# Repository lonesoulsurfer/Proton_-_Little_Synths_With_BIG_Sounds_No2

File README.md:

# Proton - Little Synths With BIG Sounds #2

This is the 2nd in a series of little synths that I'll be publishing over the next couple builds. Like my Elements synth, I've kept everything as simple as possible on this build so anyone with a soldering iron and basic soldering skills can make it. I've done away with a case and fancy power supplies to keep the build simple.

Props to Synther Jack (https://syntherjack.net/totoro-1-ic-simple-synth/) who designed this amazing little synth. All I've done is redesigned the PCB and created a front panel. I've also done a couple of mods and have included these on this build. Please check out Synther Jacks write up if you want a thorough run through on how the synth works.

The synth runs off 1 IC which is an incredible feat when you consider the amazing sounds this beast can produce. The other amazing thing about this synth is it only needs 2 X AA batteries to power it!

It's a blast to play with and can be connected to a sequencer which really shows off the sounds this little synth is capable of producing. If you don't have a sequencer then don't worry - it's still tonnes of fun to play.

Instructables step by step guide: https://www.instructables.com/Proton-Little-Synths-With-BIG-Sounds-2/

YouTube vid: https://www.youtube.com/watch?v=9Ci_B_42n48

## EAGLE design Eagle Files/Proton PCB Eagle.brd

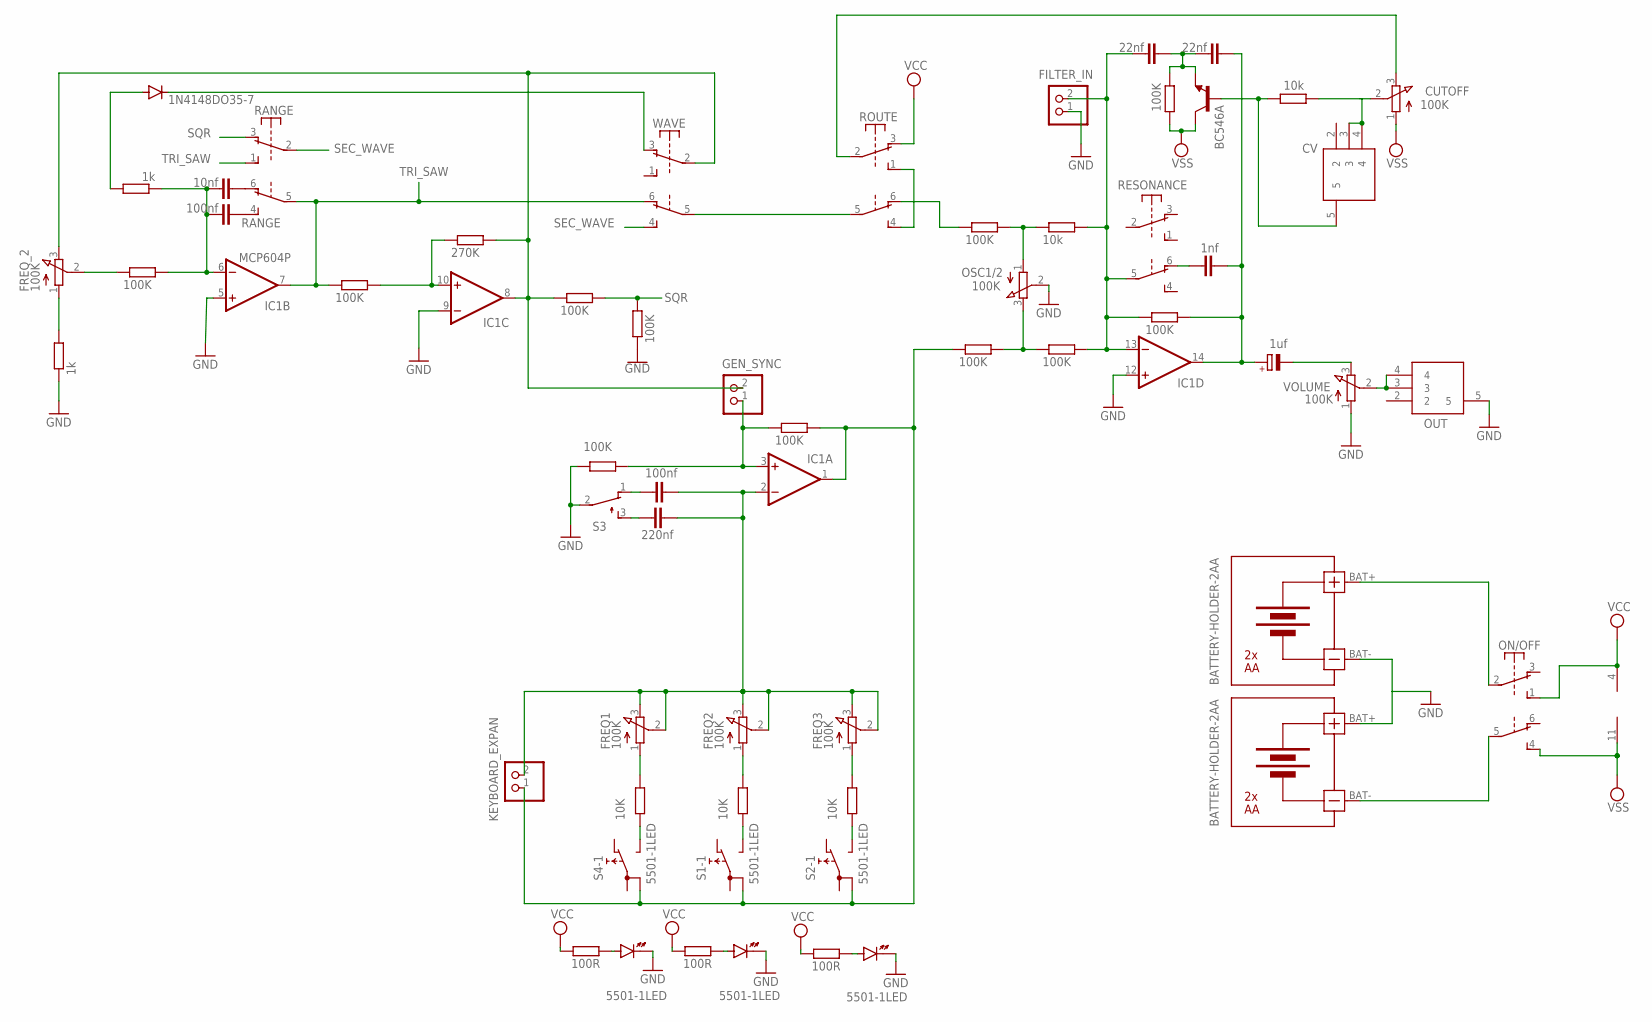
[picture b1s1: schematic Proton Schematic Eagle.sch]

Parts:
1K, 1K1: 1k; 0207/10
100K, 100K1, 100K3, 100K4, 100K5, 100K7, 100K8, 100K9, 100K11, 100K12, 100K13: 100K; 0207/10
100K2: 270K; 0207/10
100K6, 100K10: 10k; 0207/10
100K14, 100K15, 100K16: 10K; 0207/10
100K18, 100K19, 100K20: 100R; 0207/10
C1, C7: 100nf; C050-024X044
C2: 10nf; C050-024X044
C3, C4: 22nf; C050-024X044
C5: 1nf; C050-024X044
C6: 220nf; C050-024X044
C8: 1uf; E2,5-5
CUTOFF: 100K; EVUFXM
CV: PJ-320A; PJ320A
D1: 1N4148DO35-7; DO35-7
FILTER_IN: PINHD-1X2; 1X02
FREQ1, FREQ2, FREQ3: 100K; EVUFXM
FREQ_2: 100K; EVUFXM
GEN_SYNC: PINHD-1X2; 1X02
IC1: MCP604P; DIL14
KEYBOARD_EXPAN: PINHD-1X2; 1X02
ON/OFF: SWITCH-6PIN
OSC1/2: 100K; EVUFXM
OUT: PJ-320A; PJ320A
Q1: BC546A; TO92-EBC
RANGE: SWITCH-6PIN
RESONANCE: SWITCH-6PIN
ROUTE: SWITCH-6PIN
S1, S2, S4: 5501-1LED
S3: TL32YO; TL3XYO
U$1, U$2: BATTERY-HOLDER-2AA
VOLUME: 100K; EVUFXM
WAVE: SWITCH-6PIN

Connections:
GND: 1K.1, 100K4.1, 100K13.1, FILTER_IN.1, IC1.5 (+IN), IC1.9 (-IN), IC1.12 (+IN), OSC1/2.2 (S), OUT.5, S1.- (K), S2.- (K), S3.2, S4.- (K), U$1.BAT-, U$2.BAT+, VOLUME.1 (A)
unnamed: 100K1.2, 100K2.1, IC1.10 (+IN)
unnamed: 100K.1, FREQ_2.2 (S)
unnamed: 1K.2, FREQ_2.1 (A)
unnamed: C1.2, RANGE.4 (S)
unnamed: C2.2, RANGE.6 (O)
unnamed: 1K1.1, 100K.2, C1.1, C2.1, IC1.6 (-IN)
unnamed: ROUTE.5, WAVE.5
unnamed: 1K1.2, D1.A
unnamed: 100K2.2, 100K3.1, FREQ_2.3 (E), GEN_SYNC.2, IC1.8 (OUT), WAVE.2
unnamed: D1.C, WAVE.3 (O)
unnamed: ROUTE.1 (S), ROUTE.4 (S)
unnamed: 100K5.1, ROUTE.6 (O)
unnamed: 100K5.2, 100K6.1, OSC1/2.1 (A)
unnamed: 100K18.1, S4.+ (A)
unnamed: C8.-, VOLUME.3 (E)
unnamed: 100K9.2, C3.2, C4.1, Q1.E
unnamed: CUTOFF.3 (E), ROUTE.2
unnamed: C5.1, RESONANCE.6 (O)
unnamed: 100K11.2, C4.2, C5.2, C8.+, IC1.14 (OUT)
unnamed: 100K7.2, 100K8.1, OSC1/2.3 (E)
unnamed: 100K6.2, 100K8.2, 100K11.1, C3.1, FILTER_IN.2, IC1.13 (-IN), RESONANCE.5
unnamed: 100K19.1, S1.+ (A)
unnamed: 100K10.1, CV.5, Q1.B
unnamed: 100K20.1, S2.+ (A)
unnamed: 100K12.1, 100K13.2, GEN_SYNC.1, IC1.3 (+IN)
unnamed: ON/OFF.2, U$1.BAT+
unnamed: C6.2, C7.2, FREQ1.2 (S), FREQ1.3 (E), FREQ2.2 (S), FREQ2.3 (E), FREQ3.2 (S), FREQ3.3 (E), IC1.2 (-IN), KEYBOARD_EXPAN.2
unnamed: 100K14.1, S4.NO
unnamed: 100K15.1, S1.NO
unnamed: 100K16.1, S2.NO
unnamed: 100K7.1, 100K12.2, IC1.1 (OUT), KEYBOARD_EXPAN.1, S1.1B, S2.1B, S4.1B
unnamed: 100K14.2, FREQ1.1 (A)
unnamed: 100K15.2, FREQ2.1 (A)
unnamed: 100K16.2, FREQ3.1 (A)
unnamed: ON/OFF.5, U$2.BAT-
unnamed: C6.1, S3.3 (S)
unnamed: C7.1, S3.1 (O)
unnamed: OUT.3, OUT.4, VOLUME.2 (S)
unnamed: 100K10.2, CUTOFF.2 (S), CV.3, CV.4
SEC_WAVE: RANGE.2, WAVE.4 (S)
SQR: 100K3.2, 100K4.2, RANGE.3 (O)
TRI_SAW: 100K1.1, IC1.7 (OUT), RANGE.1 (S), RANGE.5, WAVE.6 (O)
VCC: 100K18.2, 100K19.2, 100K20.2, IC1.4 (V+), ON/OFF.1 (S), ROUTE.3 (O)
VSS: 100K9.1, CUTOFF.1 (A), IC1.11 (V-), ON/OFF.4 (S), Q1.C

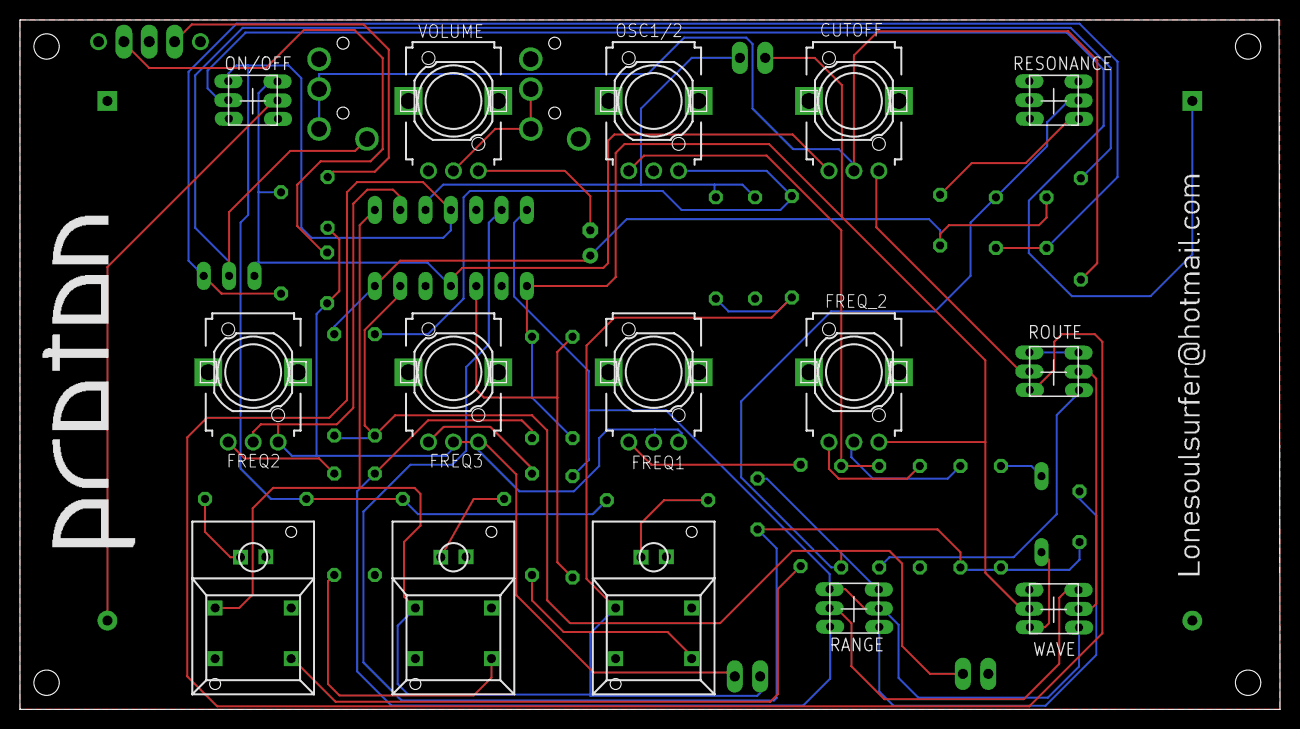
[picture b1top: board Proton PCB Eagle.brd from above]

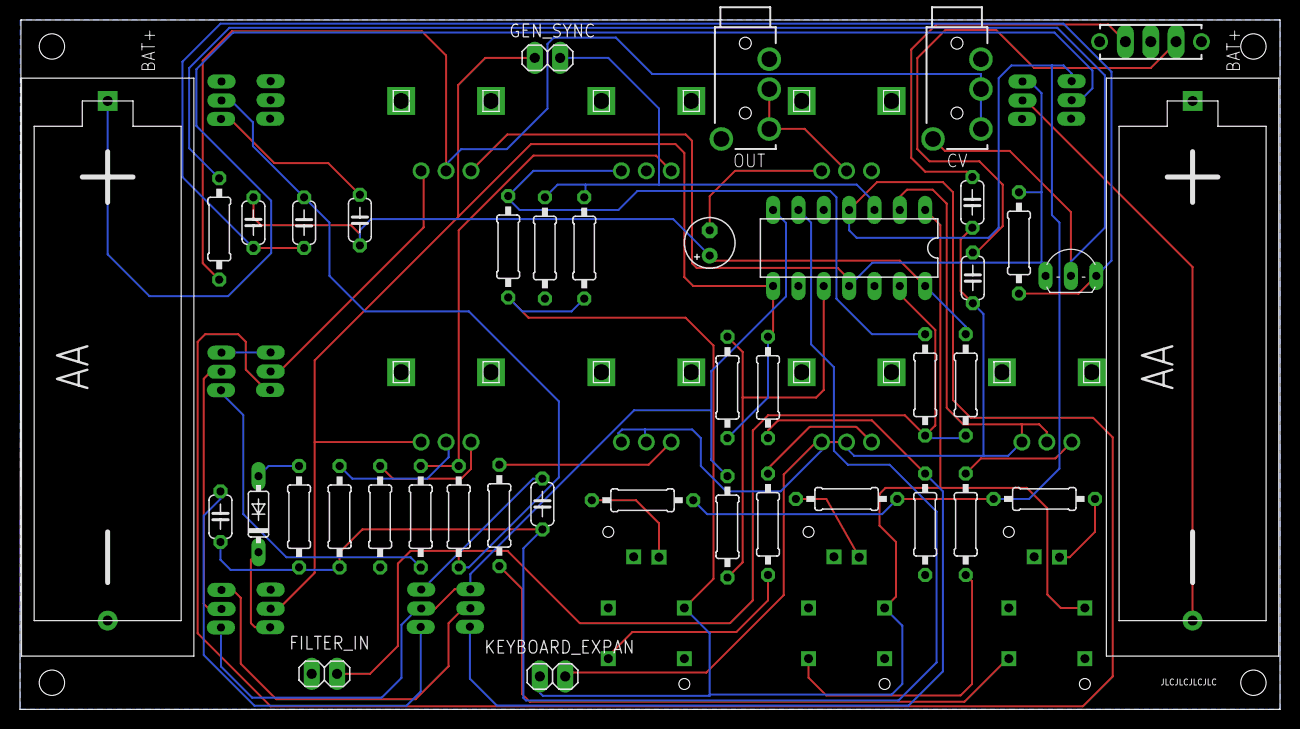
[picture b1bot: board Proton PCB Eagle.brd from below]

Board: 2 copper layers, 126.3 x 69.1 mm, 56 parts (41 on the bottom side), 45 nets.
